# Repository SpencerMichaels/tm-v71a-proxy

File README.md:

# TM-V71A display proxy

A small board that sits in the cable between a **Kenwood TM-V71A** radio and its separated control head and changes its brightness based on an external 12V input — for instance, your vehicle's ILL+.

The TM-V71A has only a single display brightness setting, which is cumbersome to change, especially if you need to operate your radio in both day and night conditions. This board stores separate brightness settings depending on whether your vehicle's headlights are on or not, and switches the control head's brightness to the corresponding setting every time you toggle the headlights.

To use, just set your preferred brightness in your TM-V71A's settings menu once with your headlights off, then again with your headlights on.

*3D render of Rev B, seen from the connector edge. J3 (grey) is a simplified stand-in model.*

## How it works

When the head is separated from the body, the two talk over a 4-wire cable: power, ground, and one serial data line in each direction (57,600 baud). The body tells the head what to show, including the display brightness, as a short message `33 <level> 0D`.

- **Power, ground and the head's key presses** pass straight through the board in copper.
- **The body's display data** goes through an AVR128DB28 microcontroller. It forwards every byte to the head as it arrives, about one byte-time (0.17 ms) late, and rewrites brightness messages on the way.
- **The vehicle's lights input** (ILL+, through an optocoupler) tells the AVR whether it's day or night. The vehicle wiring is fully isolated from the radio.
- **Learning:** set the brightness in the radio's menu once with the lights off and once with them on. The board remembers both levels in EEPROM, and sends the right one whenever the lights change or the radio powers up.
- **Power:** the board takes about 5 mA from the radio's own 10 V head supply, so it needs no other power wiring.
- **Fail-safe:** with the AVR pulled from its socket and the JP1 shunt fitted, the board is a plain pass-through.

The message format and how the radio uses it are in [docs/protocol.md](docs/protocol.md).

## Status

| | |
|---|---|
| **Rev A** (`rev-a` branch) | Built and working in the vehicle with the full firmware. Its two data lines were swapped by mistake, so it needed a small rework; the `rev-a` branch documents it. |
| **Rev B** (this branch) | Rev A with the data lines corrected, a 4-pin data-tap header (J5) for logic analyzers, and a long-lead crystal that's easier to solder. Not yet fabricated. It passes ERC, DRC with schematic parity, and 25 design checks. The firmware is shared with Rev A. |

Tested with a TM-V71A in a 2013 Toyota Tacoma. Any vehicle with a 12 V lights-on (ILL+ or TAIL) signal should work.

## Building one

1. **Order the PCB.** Upload [`hardware/fab/kenwood_proxy_revB_oshpark_gerbers.zip`](hardware/fab/kenwood_proxy_revB_oshpark_gerbers.zip) to OSH Park or any 2-layer fab: 54 × 52 mm, about $22 for three at OSH Park. See [ordering notes](hardware/fab/ORDERING.md).
2. **Order the parts.** [`BOM_upload_digikey_mouser.csv`](hardware/fab/BOM_upload_digikey_mouser.csv) uploads straight to DigiKey or Mouser. Expect about $30. All parts are through-hole.
3. **Assemble and check** with the **[assembly guide](docs/assembly.md)**. Each step has a diagram of the board with that step's parts highlighted, and the guide has the meter and power checks to do before connecting the radio.
4. **Program it** with a 5 V SerialUPDI adapter: see [firmware/README.md](firmware/README.md).
5. **Print the case** (PETG or ASA) from [`hardware/enclosure/`](hardware/enclosure/): two parts, no supports, 4 × M3 screws.

6. **Install.** Body cable → J1, head cable → J2. J3 → the vehicle's ILL+ (live with the parking lights) and chassis ground. Then set the brightness once with the lights off and once with them on.

## Repository layout

| Path | What |
|---|---|
| [`hardware/`](hardware/) | KiCad 10 project, Gerbers, BOMs, design checks, SPICE simulation, and the generator scripts. [Design notes](hardware/README.md). |
| [`hardware/enclosure/`](hardware/enclosure/) | Case STLs and STEP, plus the FreeCAD generator script |
| [`firmware/`](firmware/) | AVR firmware (arduino-cli + DxCore), host unit tests, serial tools |
| [`docs/assembly.md`](docs/assembly.md) | Rev B assembly and checks |
| [`docs/protocol.md`](docs/protocol.md) | The head ↔ body link, as measured |
| [`docs/captures/`](docs/captures/) | Raw captures of the radio's traffic |
| [`docs/research/`](docs/research/) | Service-manual notes on the radio's interface and the Tacoma lighting circuit |

## Safety notes

- The cable's PB line carries about 10 V. A reversed or miswired 4P4C coupler can put it on a data pin of the head. The assembly guide checks every J2 pin before the head is connected.
- **Fit the JP1 shunt only with the AVR removed.**
- The board never draws power from vehicle wiring. The lights input is opto-isolated and simulated to survive reversed wiring, 24 V and a 40 V load dump.

## License

- **Hardware** (everything under `hardware/` except the Python scripts: schematic, PCB, Gerbers, BOMs, case models): [CERN-OHL-S-2.0](LICENSE-HARDWARE).
- **Firmware, scripts and tools:** [GPL-3.0](LICENSE).
- **Documentation:** follows the hardware or software it describes.

## Credits

- The brightness message format was first published by [KK4HEJ](https://kk4hej.wordpress.com/decoding-the-tm-v71a-display-protocol/).
- The 4P4C jack footprint follows Würth Elektronik's [KiCad library](https://github.com/WurthElektronik/KiCad-Library).
- Built with KiCad, Freerouting, ngspice, FreeCAD and DxCore.

Kenwood and TM-V71A are trademarks of JVCKENWOOD Corporation. This project isn't affiliated with or endorsed by Kenwood.

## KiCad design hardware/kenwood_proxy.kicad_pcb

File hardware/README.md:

# Hardware: Rev B

The KiCad 10 project for the proxy board: a 54 × 52 mm, 2-layer, all-through-hole board for hand assembly.

| File | What |
|---|---|
| `kenwood_proxy.kicad_pro` / `.kicad_sch` / `.kicad_pcb` | The KiCad project, with three schematic sheets |
| `fab/` | Gerbers (OSH Park zip), BOMs, [ordering notes](fab/ORDERING.md) |
| `enclosure/` | 3D-printable case: STL, STEP and the generator; see its [README](enclosure/README.md) |
| `checks/` | Schematic PDF, layout PDF (1:1), ERC/DRC reports, design-check results, netlist |
| `build_schematic.py`, `build_board.py`, `check_design.py` | Scripts that generate and check the design (see [Rebuilding](#rebuilding)) |
| `simulation/`, [`simulation_review.md`](simulation_review.md) | ngspice checks of the interface, ILL input and power networks |
| `footprints/`, `Kenwood_Proxy.kicad_sym` | Project footprint (4P4C jack) and symbol library |
| `3dmodels/` | Simplified Micro-Fit (J3) model and its generator, since KiCad's library has none |

**Rev B status.** Rev B is Rev A with three changes:
- the data-line fix
- the J5 tap header
- a long-lead crystal

The design has been verified on a **reworked Rev A board** in a vehicle, and the firmware is the same. Rev B itself hasn't been fabricated yet. It passes ERC, DRC with schematic parity, and the design checks.

## Circuit

| Block | What it does |
|---|---|
| **Pass-through** | J1 (BODY) and J2 (HEAD) are Würth 615004143821 4P4C jacks. PB (pin 1), GND (pin 2) and the head → body data line (pin 4) run straight through in copper. |
| **Proxy, body → head** | The body's data (J1 pin 3) goes only to the AVR, through R6 10 kΩ. The AVR re-sends every byte to the head (J2 pin 3) on USART1 TX through R2 470 Ω, rewriting brightness messages on the way. |
| **Idle and reset** | The head's input has its own 47 kΩ pull-up. While the AVR is in reset, being programmed or removed, the line idles high and the display keeps its last content. |
| **JP1 bypass** | Recovery only: **remove U1, then fit the shunt** to connect body data straight to the head. With U1 running, JP1 makes the AVR and the body fight over the line. Nothing is damaged (simulated peaks are 10 mA at the AVR pin and 5 mA at the body's driver), but the data is garbled. |
| **Power** | PB (about 10 V from the radio's regulator) → R1 150 Ω 1 W → RC filter (C6, C5) → LM2936Z-5.0 → 5 V. Draws about 5 mA. The board never takes power from vehicle wiring. R1 limits fault current, and the voltage across it ÷ 150 gives the board's current. |
| **Lights input** | J3 (Molex Micro-Fit 3.0, latching): pin 1 ILL+, pin 2 GND. R9 2.2 kΩ, R10 680 Ω shunt, D1 reverse protection, then an SFH617A-3 optocoupler. ILL_SENSE (PD1) reads low when the lights are on. The vehicle side is isolated from the radio's ground. |
| **J4: programming** | 1 GND, 2 UPDI, 3 DBG_TX (event log, through R13). |
| **J5: data taps** | 1 GND, 2 body → head (through R6), 3 head → body (through R7), 4 what the head receives (after R2). Listen only. |
| **Crystal** | Y1, 32.768 kHz, auto-tunes the AVR's internal 20 MHz oscillator, so the UART timing holds over temperature. |

**Lights input, simulated:**
- reads low (0.36 V or less) with ILL+ from 9 V upward
- reads high (5.0 V) with ILL+ at 2 V or below
- survives reversed wiring (D1), 24 V, and a 40 V load dump (R9 is rated 0.5 W)

## MCU pins (AVR128DB28, SPDIP-28)

| Pin | Port | Function |
|---|---|---|
| 23 | PA1 | USART0 RX ← body data, through R6 |
| 22 | PA0 | USART0 TX → DBG_TX on J4 pin 3 (event log, 57,600 baud) |
| 2 | PC0 | USART1 TX → R2 → head's data input |
| 3 | PC1 | head → body data, through R7 (logging only) |
| 7 | PD1 | ILL_SENSE (low = lights on) |
| 16 / 17 | PF0 / PF1 | 32.768 kHz crystal |
| 19 | UPDI | J4 pin 2 |
| 6, 14, 20 / 15, 21 | | 5 V / GND |
| others | PA2–PA7, PC2–PC3, PD2–PD7 | unused; the firmware enables pull-ups |

## Interface levels

Taken from the TM-V71A service manual; see [`docs/research/`](../docs/research/).
- **Body transmit:** a TC74HC4050 buffer through a 1 kΩ resistor.
- **Body receive:** through a 1 kΩ resistor with a 47 kΩ pull-up.
- **Head receive:** a TC4S81F gate with a 47 kΩ pull-up and a varistor.

Simulated against those values:
- the proxy's low level at the head is 0.06 V
- the low level through the JP1 bypass is 0.11 V
- JP1 fitted with U1 running gives a steady 3.5 mA of contention, which is safe

Cable corners from 100 pF to 470 pF were simulated: the default installation (a 4 m body cable, a 0.3 m head cable) plus those extremes.

## PCB layout

- **Edges:** J1, J2 and J3 sit on the top edge, with the jack faces flush. J4 is at the bottom left, J5 at the top left, and the power section runs along the bottom. There's an M3 mounting hole in each corner.
- **Routing:** Freerouting 2.1.0, plus hand-routed ILL nets.
  - Track widths: PB, PB_FILT and +5 V are 0.6 mm; signals 0.3 mm; ILL nets 0.4 mm.
  - GND pours on both layers, with stitching vias on a 3 mm grid.
- **ILL isolation:** the ILL area (top right, outlined on the silkscreen) has no pour and no other tracks. `kenwood_proxy.kicad_dru` enforces at least 2.0 mm from the ILL nets to all other copper, and the layout gives about 2.5 mm.
- **Checks:** DRC with schematic parity gives 0 violations, 0 unconnected and 0 parity errors (`checks/pcb-drc.json`). The design checks pass 25/25 (`checks/design_checks.json`).
- **3D models:**
  - The jacks use Würth's STEP model through `${WE_3DMODEL_DIR}`. Install [WurthElektronik/KiCad-Library](https://github.com/WurthElektronik/KiCad-Library) and set that path variable in KiCad to see them.
  - Y1 uses KiCad's near-identical C26-LF crystal model.
  - J3 uses `3dmodels/Molex_Micro-Fit_3.0_43045-0200_simplified.step`.
- **Jack footprint:** matches Würth's official KiCad footprint `J_Wurth_WR-MJ_615004143821` ([WurthElektronik/KiCad-Library](https://github.com/WurthElektronik/KiCad-Library)), rotated 180° and with 1.5 mm pads.

## Rebuilding

The schematic and board are generated by scripts. Edit the scripts rather than the KiCad files: **re-running a script overwrites GUI edits.**

```sh
python3 build_schematic.py                       # schematic, symbol library, design_intent.json
python3 check_design.py                          # netlist + ERC + 25 design checks -> checks/
KPY=/Applications/KiCad/KiCad.app/Contents/Frameworks/Python.framework/Versions/Current/bin/python3
$KPY build_board.py                              # placement -> checks/placement.dsn
java -jar freerouting-2.1.0.jar -de checks/placement.dsn -do checks/routing.ses -mp 40 --gui.enabled=false
$KPY build_board.py --session checks/routing.ses # import routing, pours, hand fixes
kicad-cli pcb drc --schematic-parity -o checks/pcb-drc.json kenwood_proxy.kicad_pcb
```

`build_board.py` hand-routes one PB link beside J4 that Freerouting leaves unrouted. The paths in it assume the macOS KiCad install; adjust them for other platforms.

## Possible future work

- **Follow the dash dimmer.** Wire J3 across ILL+ and ILL− instead of ILL+ and GND. The opto output then follows the dimmer's PWM, so the AVR could time the duty cycle and map it to brightness 0–8.
  - Reported automotive dimmer frequencies are 100 Hz–1 kHz, which the SFH617A and the 10 kΩ pull-up can follow, so this would be firmware-only.
  - The current firmware's 50 ms "stable" filter assumes a steady input, so it would need changing.
  - Measure the dimmer's frequency first.
- **Auto power-on** needs no hardware: the radio resumes its on/off state when DC returns, so an ACC-switched supply is enough.

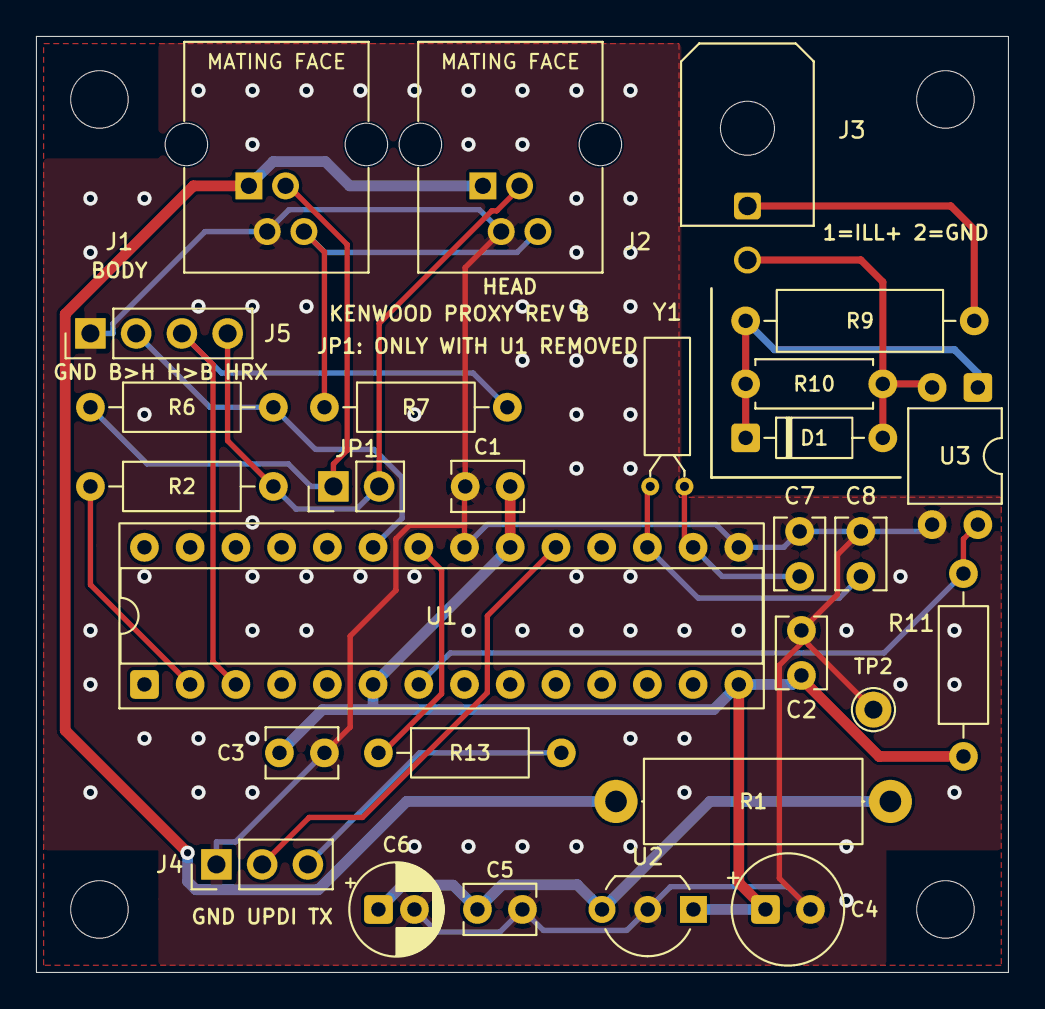
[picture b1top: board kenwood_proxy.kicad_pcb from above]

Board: 2 copper layers, 54.0 x 52.0 mm, 32 parts (0 on the bottom side), 19 nets.

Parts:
C1, C2, C3, C5: 100nF 50V X7R; C_Disc_D3.8mm_W2.6mm_P2.50mm
C4: 22uF 16V tantalum; CP_Radial_Tantal_D6.0mm_P2.50mm
C6: 10uF 25V 105C; CP_Radial_D5.0mm_P2.00mm
C7, C8: 15pF C0G; C_Disc_D3.8mm_W2.6mm_P2.50mm
D1: 1N4148; D_DO-35_SOD27_P7.62mm_Horizontal
H1, H2, H3, H4: M3; MountingHole_3.2mm_M3
J1: KENWOOD BODY; Wurth_615004143821_4P4C_TabUp
J2: KENWOOD HEAD; Wurth_615004143821_4P4C_TabUp
J3: ILL+ / GND; Molex_Micro-Fit_3.0_43045-0200_2x01_P3.00mm_Horizontal
J4: PROG/DEBUG; PinHeader_1x03_P2.54mm_Vertical
J5: DATA TAPS; PinHeader_1x04_P2.54mm_Vertical
JP1: HARD BYPASS; PinHeader_1x02_P2.54mm_Vertical
R1: 150R 1W; R_Axial_DIN0414_L11.9mm_D4.5mm_P15.24mm_Horizontal
R2, R13: 470R; R_Axial_DIN0207_L6.3mm_D2.5mm_P10.16mm_Horizontal
R6, R7, R11: 10k; R_Axial_DIN0207_L6.3mm_D2.5mm_P10.16mm_Horizontal
R9: 2.2k; R_Axial_DIN0309_L9.0mm_D3.2mm_P12.70mm_Horizontal
R10: 680R; R_Axial_DIN0207_L6.3mm_D2.5mm_P7.62mm_Horizontal
TP2: GND; TestPoint_THTPad_D2.0mm_Drill1.0mm
U1: AVR128DB28-I/SP; DIP-28_W7.62mm_Socket
U2: LM2936Z-5.0; TO-92_Inline_Wide
U3: SFH617A-3; DIP-4_W7.62mm
Y1: 32.768kHz 12.5pF; Crystal_DS26_D2.0mm_L6.0mm_Horizontal

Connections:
+5V: C1.1, C2.1, C3.1, C4.1, R11.1, U1.6 (VDDIO2), U1.14 (AVDD), U1.20 (VDD), U2.1 (VO)
BODY_TXD: J1.3 (DATA_body-to-head), JP1.1, R6.1
DBG_TX: J4.3, R13.2
DBG_TX_MCU: R13.1, U1.22 (XTALHF1/PA0)
GND: C1.2, C2.2, C3.2, C4.2, C5.2, C6.2, C7.2, C8.2, J1.2 (GND), J2.2 (GND), J4.1, J5.1, TP2.1, U1.15 (AGND), U1.21 (GND), U2.2 (GND), U3.3
HEAD_RXD: J2.3 (DATA_body-to-head), J5.4, JP1.2, R2.2
HEAD_TXD: J1.4 (DATA_head-to-body), J2.4 (DATA_head-to-body), R7.1
HEAD_TX_MCU: R2.1, U1.2 (PC0)
ILL_GND: D1.2 (A), J3.2, R10.2, U3.2
ILL_LED_A: D1.1 (K), R9.2, R10.1, U3.1
ILL_P: J3.1, R9.1
ILL_SENSE: R11.2, U1.7 (PD1), U3.4
PB: J1.1 (PB), J2.1 (PB), R1.1
PB_FILT: C5.1, C6.1, R1.2, U2.3 (VI)
TAP_BODY: J5.2, R6.2, U1.23 (XTALHF2/PA1)
TAP_HEAD: J5.3, R7.2, U1.3 (PC1)
UPDI: J4.2, U1.19 (UPDI)
XTAL32K1: C7.1, U1.16 (XTAL32K1/PF0), Y1.1
XTAL32K2: C8.1, U1.17 (XTAL32K2/PF1), Y1.2

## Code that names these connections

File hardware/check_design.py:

"""Kenwood proxy design checks. Exports the native KiCad netlist and ERC, then checks
pin-level connectivity against design_intent.json plus explicit safety requirements.
Does not simulate parts; electrical limits below are hand calculations from datasheets.
"""
from pathlib import Path
import json, subprocess, xml.etree.ElementTree as ET

HERE = Path(__file__).resolve().parent
CHK = HERE/'checks'; CHK.mkdir(exist_ok=True)
SCH = HERE/'kenwood_proxy.kicad_sch'
subprocess.run(['kicad-cli','sch','export','netlist','--format','kicadxml','-o',str(CHK/'netlist.xml'),str(SCH)],check=True,capture_output=True)
subprocess.run(['kicad-cli','sch','erc','--format','json','--severity-all','-o',str(CHK/'erc.json'),str(SCH)],check=True,capture_output=True)

intent = json.loads((HERE/'design_intent.json').read_text())
root = ET.parse(CHK/'netlist.xml').getroot()
actual = {}; nets = {}
for n in root.iter('net'):
    name = n.get('name').lstrip('/')
    for nd in n.iter('node'):
        actual[(nd.get('ref'), nd.get('pin'))] = name
        nets.setdefault(name, set()).add((nd.get('ref'), nd.get('pin')))

results = []
def check(name, ok, detail=''):
    results.append({'check': name, 'pass': bool(ok), 'detail': detail})

# 1. ERC clean
erc = json.loads((CHK/'erc.json').read_text())
viol = [v for s in erc['sheets'] for v in s['violations']]
check('ERC: zero violations', not viol, '; '.join(v['description'] for v in viol))

# 2. Every intended pin is on its intended net (unconnected pins must be absent or single-pin)
bad = []
for ref, c in intent.items():
    if ref.startswith('#'): continue
    for pin, p in c['pins'].items():
        got = actual.get((ref, pin))
        want = p['net']
        if want is None:
            if got is not None and len(nets.get(got, ())) > 1: bad.append(f'{ref}.{pin} should be NC, is on {got}')
        elif got != want: bad.append(f'{ref}.{pin} want {want} got {got}')
check('Netlist parity with design intent', not bad, '; '.join(bad))

def on(net, ref, pin): return (ref, pin) in nets.get(net, set())

# 3. Jack pin mapping (Wurth numbering, user-confirmed physical order)
for j in ('J1', 'J2'):
    check(f'{j} pin1 PB / pin2 GND / pin3 HEAD_TXD',
          actual.get((j,'1'))=='PB' and actual.get((j,'2'))=='GND' and actual.get((j,'3'))=='HEAD_TXD')
check('J1 pin4 = BODY_TXD, J2 pin4 = HEAD_RXD (no TX/RX crossover)', actual.get(('J1','4'))=='BODY_TXD' and actual.get(('J2','4'))=='HEAD_RXD')
check('HEAD_TXD direct copper J2.3 to J1.3', on('HEAD_TXD','J1','3') and on('HEAD_TXD','J2','3'))

# 4. PB never touches any MCU, opto, or signal net; PB only reaches U2 through R1
pb_nets = {'PB','PB_FILT'}
pb_refs = {r for n in pb_nets for r,_ in nets.get(n,())}
check('PB nets touch only jacks, R1, C5, C6, U2 and PWR_FLAG', pb_refs <= {'J1','J2','R1','C5','C6','U2','#FLG1'}, str(sorted(pb_refs)))
check('PB direct copper J1.1 to J2.1; board supply via R1', on('PB','J1','1') and on('PB','J2','1') and on('PB','R1','1') and on('PB_FILT','R1','2'))

# 5. Full-proxy data path: body -> MCU (tap) -> R2 -> head; JP1 is the only direct body/head bridge
hr = nets['HEAD_RXD']
check('HEAD_RXD connections limited to J2, JP1, R2', {r for r,_ in hr} <= {'J2','JP1','R2'}, str(sorted(hr)))
check('BODY_TXD connections limited to J1, JP1, R6 (tap)', {r for r,_ in nets['BODY_TXD']} <= {'J1','JP1','R6'}, str(sorted(nets['BODY_TXD'])))
check('Proxy output: U1 pin 2 (PC0, USART1 TX) -> R2 -> HEAD_RXD', on('HEAD_TX_MCU','U1','2') and on('HEAD_TX_MCU','R2','1') and on('HEAD_RXD','R2','2') and {r for r,_ in nets['HEAD_TX_MCU']} <= {'U1','R2'})
check('JP1 hard bypass is the only part bridging BODY_TXD and HEAD_RXD', ({r for r,_ in nets['BODY_TXD']} & {r for r,_ in nets['HEAD_RXD']}) == {'JP1'} and on('BODY_TXD','JP1','1') and on('HEAD_RXD','JP1','2'))
check('No U1 pin directly on any radio-line net', not any(r=='U1' for n in ('BODY_TXD','HEAD_RXD','HEAD_TXD') for r,_ in nets.get(n,())))

# 6. ILL isolation: ILL_P/ILL_GND/ILL_LED_A never touch board nets
ill = {'ILL_P','ILL_GND','ILL_LED_A'}
ill_refs = {(r,p) for n in ill for r,p in nets.get(n,())}
check('ILL side isolated (only J3, R9, R10, D1, U3 LED pins)', {r for r,_ in ill_refs} <= {'J3','R9','R10','D1','U3'} and not ({('U3','3'),('U3','4')} & ill_refs))

# 7. UART pin plan matches AVR DB SPDIP-28 multiplexing (DS40002247B table 3-1)
plan = {'23':'TAP_BODY','22':'DBG_TX_MCU','3':'TAP_HEAD','2':'HEAD_TX_MCU','16':'XTAL32K1','17':'XTAL32K2','19':'UPDI'}
check('U1 USART0 PA1/PA0, USART1 PC1/PC0, XOSC32K PF0/PF1, UPDI', all(actual.get(('U1',k))==v for k,v in plan.items()))
check('U1 VDD/AVDD/VDDIO2 on +5V, GND/AGND on GND', all(actual.get(('U1',k))=='+5V' for k in ('6','14','20')) and all(actual.get(('U1',k))=='GND' for k in ('15','21')))

# 8. Hand calculations (datasheet values)
calc = {}
Vb = 5.0
R956 = 1000   # body TXD series resistor inside the radio (service manual p.84, IC951 3Y -> R956 1k -> J952-4)
R2 = 470; RPU_HEAD = 47000; ROUT_MCU_MAX = 117   # head CP913 pull-up (p.74); AVR output resistance worst case (VDD-0.7 V at 6 mA)
calc['proxy_low_at_head_V'] = 5.25*(R2+ROUT_MCU_MAX)/(R2+ROUT_MCU_MAX+RPU_HEAD)       # MCU low against head pull-up
calc['proxy_head_rc_us'] = (R2+ROUT_MCU_MAX)*570e-12*1e6                                # worst head-side C: 470 pF cable + 100 pF varistor
calc['jp1_with_u1_contention_mA'] = 5.25/(R956+25+R2+25)*1000                           # JP1 fitted while U1 still drives (misuse)
calc['jp1_bypass_low_at_head_V'] = 5.25*(R956+25)/(R956+25+RPU_HEAD)                    # U1 removed, JP1 fitted
def rv(ref):
    x = intent[ref]['value'].split()[0].lower()
    return float(x[:-1])*1e3 if x.endswith('k') else float(x.rstrip('r'))
R9, R10 = rv('R9'), rv('R10')
calc['ill_led_mA_at_13V'] = (13-1.15)/R9*1000 - 1.15/R10*1000
calc['ill_led_mA_at_9V'] = (9-1.15)/R9*1000 - 1.15/R10*1000
calc['ill_R9_W_at_14V'] = ((14-1.15)/R9)**2*R9
calc['ill_led_mA_at_2V'] = max(0.0, (2.0-1.15)/R9*1000 - 1.15/R10*1000)   # ILL+ residual/floating 2 V with lights off: R10 shunts all of it
calc['pb_fault_current_mA_R1_short'] = 10/150*1000
calc['R1_fault_W'] = 10**2/150
calc['est_board_current_mA'] = {'mcu_20MHz_active_typ':4.4,'ldo_iq':0.2,'opto_pullup_max':0.5,'taps':0.0}
calc['est_board_total_mA'] = round(sum(calc['est_board_current_mA'].values()),2)
check('Proxy low level at head < 1.5 V (TC4S81F VIL max)', calc['proxy_low_at_head_V'] < 1.5, f"{calc['proxy_low_at_head_V']:.2f} V")
check('Proxy edge RC at head < 1 us (bit = 17.4 us)', calc['proxy_head_rc_us'] < 1.0, f"{calc['proxy_head_rc_us']:.2f} us")
check('JP1 fitted with U1 present: contention <= 4 mA (HC4050 recommended)', calc['jp1_with_u1_contention_mA'] <= 4.0, f"{calc['jp1_with_u1_contention_mA']:.2f} mA")
check('JP1 bypass (U1 removed) low level at head < 1.5 V', calc['jp1_bypass_low_at_head_V'] < 1.5, f"{calc['jp1_bypass_low_at_head_V']:.2f} V")
check('ILL LED off with ILL+ at 2 V (lights off)', calc['ill_led_mA_at_2V'] == 0.0, f"{calc['ill_led_mA_at_2V']:.2f} mA")
check('ILL LED current >= 1.0 mA at 9 V input', calc['ill_led_mA_at_9V'] >= 1.0, f"{calc['ill_led_mA_at_9V']:.2f} mA")
check('Estimated board draw <= 10 mA PB target', calc['est_board_total_mA'] <= 10, f"{calc['est_board_total_mA']} mA (typical, not measured)")

out = {'results': results, 'calculations': calc, 'net_count': len(nets)}
(CHK/'design_checks.json').write_text(json.dumps(out, indent=2)+'\n')
for r in results: print(('PASS ' if r['pass'] else 'FAIL ')+r['check']+(' -- '+r['detail'] if r['detail'] and not r['pass'] else (' ('+r['detail']+')' if r['detail'] else '')))
print(f"{sum(r['pass'] for r in results)}/{len(results)} checks passed")
raise SystemExit(0 if all(r['pass'] for r in results) else 1)

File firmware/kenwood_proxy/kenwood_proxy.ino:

/* Kenwood TM-V71A proxy firmware, AVR128DB28 (DxCore).
 *
 * Pins (see hardware/README.md):
 *   Rev B (KP_BODY_ON_USART1 = 0, default):
 *     PA1 USART0 RX  <- R6 <- J1 pin 3 (body -> head stream)
 *     PC0 USART1 TX  -> R2 470 ohm -> J2 pin 3 (head RX, proxy output)
 *     PC1            <- R7 <- cable pin 4 (head -> body, passes straight through; unused)
 *   Reworked Rev A (KP_BODY_ON_USART1 = 1, rev-a branch):
 *     PC1 USART1 RX  <- R7 <- J1 pin 3 (body -> head stream)
 *     PC0 USART1 TX  -> 470 ohm -> J2 pin 3
 *   PA0 USART0 TX  -> DBG_TX on J4 pin 3 (event log, radio baud)
 *   PD1            <- ILL_SENSE (low = lights on)
 *   PF0/PF1        32.768 kHz crystal: auto-tunes the internal oscillator
 *
 * All packet decisions live in proxy_core.c (host-tested). This file only moves
 * bytes, samples the lights input, stores EEPROM and kicks the watchdog. Arduino's
 * Serial is not used, so the USART interrupts below are the only ones.
 */
#include <avr/io.h>
#include <avr/interrupt.h>
#include <avr/eeprom.h>
extern "C" {
#include "proxy_core.h"
}

static kp_proxy_t P;

/* ---------------------------------------------------------------- EEPROM */
/* Layout: magic, version, slot day, slot night, last body level, checksum. */
#define EE_MAGIC 0x4B   /* 'K' */
#define EE_VER   1
static uint8_t ee_sum(const kp_persist_t *s) { return (uint8_t)(EE_MAGIC ^ s->slot[0] ^ (s->slot[1] << 1) ^ (s->last_body << 2) ^ 0x5A); }

static void ee_load(kp_persist_t *s)
{
    s->slot[0] = eeprom_read_byte((uint8_t *)2);
    s->slot[1] = eeprom_read_byte((uint8_t *)3);
    s->last_body = eeprom_read_byte((uint8_t *)4);
    if (eeprom_read_byte((uint8_t *)0) != EE_MAGIC || eeprom_read_byte((uint8_t *)1) != EE_VER ||
        eeprom_read_byte((uint8_t *)5) != ee_sum(s))
        s->slot[0] = s->slot[1] = s->last_body = KP_UNSET;   /* blank or corrupt: start fresh */
}

static void ee_store(const kp_persist_t *s)
{
    /* update_byte skips unchanged cells. Interrupts stay on, so forwarding continues. */
    eeprom_update_byte((uint8_t *)0, EE_MAGIC);
    eeprom_update_byte((uint8_t *)1, EE_VER);
    eeprom_update_byte((uint8_t *)2, s->slot[0]);
    eeprom_update_byte((uint8_t *)3, s->slot[1]);
    eeprom_update_byte((uint8_t *)4, s->last_body);
    eeprom_update_byte((uint8_t *)5, ee_sum(s));
}

/* ---------------------------------------------------------------- debug log */
static uint8_t dbg[64];
static volatile uint8_t dbg_head, dbg_tail;

static void dbg_putc(uint8_t c)
{
    uint8_t next = (dbg_head + 1) & 63;
    if (next == dbg_tail) return;              /* log is best effort */
    dbg[dbg_head] = c;
    dbg_head = next;
    USART0.CTRLA |= USART_DREIE_bm;
}

static void on_event(uint8_t ev, uint8_t a, uint8_t b)
{
    /* Called from the RX interrupt or with interrupts off: keep it short. */
    if (KP_SNIFF) return;                      /* sniff build: DBG_TX carries raw body bytes only */
    dbg_putc(ev);
    if (a) { dbg_putc(' '); dbg_putc(a); }
    if (b) { dbg_putc(' '); dbg_putc(b); }
    dbg_putc('\r');
    dbg_putc('\n');
}

static void dbg_str(const char *s)
{
    if (KP_SNIFF) return;
    uint8_t sreg = SREG;
    cli();
    while (*s) dbg_putc((uint8_t)*s++);
    SREG = sreg;
}

static char lvl_char(uint8_t v) { return v == KP_UNSET ? '-' : (char)v; }

/* ---------------------------------------------------------------- interrupts */
#if KP_BODY_ON_USART1
#define BODY_USART USART1
ISR(USART1_RXC_vect)
#else
#define BODY_USART USART0
ISR(USART0_RXC_vect)
#endif
{
    BODY_USART.RXDATAH;                        /* status first; a framing error is forwarded as received */
    uint8_t b = BODY_USART.RXDATAL;
    if (KP_SNIFF) dbg_putc(b);                 /* same baud in and out, so the copy keeps up */
    kp_body_byte(&P, b, millis());
    USART1.CTRLA |= USART_DREIE_bm;
}

ISR(USART1_DRE_vect)
{
    int c = kp_next_head_byte(&P);
    if (c < 0) USART1.CTRLA &= ~USART_DREIE_bm;
    else USART1.TXDATAL = (uint8_t)c;
}

ISR(USART0_DRE_vect)
{
    if (dbg_tail == dbg_head) { USART0.CTRLA &= ~USART_DREIE_bm; return; }
    USART0.TXDATAL = dbg[dbg_tail];
    dbg_tail = (dbg_tail + 1) & 63;
}

/* ---------------------------------------------------------------- setup */
static uint8_t lights_on(void) { return !(VPORTD.IN & PIN1_bm); }

static void clocks(void)
{
    /* 20 MHz internal (FQBN clock=20internal), auto-tuned against the 32.768 kHz crystal.
     * 20 MHz keeps clock harmonics off 144-148 MHz. */
    _PROTECTED_WRITE(CLKCTRL.XOSC32KCTRLA, CLKCTRL_ENABLE_bm | CLKCTRL_CSUT_1K_gc);
    _PROTECTED_WRITE(CLKCTRL.OSCHFCTRLA, CLKCTRL.OSCHFCTRLA | CLKCTRL_AUTOTUNE_bm);
}

static void pins(void)
{
    /* Unused I/O: pull-ups on so nothing floats. */
    for (uint8_t i = 2; i < 8; i++) (&PORTA.PIN0CTRL)[i] = PORT_PULLUPEN_bm;   /* PA2-PA7 */
    PORTC.PIN2CTRL = PORT_PULLUPEN_bm;
    PORTC.PIN3CTRL = PORT_PULLUPEN_bm;
    for (uint8_t i = 2; i < 8; i++) (&PORTD.PIN0CTRL)[i] = PORT_PULLUPEN_bm;   /* PD2-PD7 */
    /* PD1 ILL_SENSE has R11; PC1 TAP_HEAD is driven through R7. Plain inputs. */
    PORTA.OUTSET = PIN0_bm;  PORTA.DIRSET = PIN0_bm;    /* DBG_TX idles high */
    PORTC.OUTSET = PIN0_bm;  PORTC.DIRSET = PIN0_bm;    /* head RX idles high: no glitch at start */
}

static void uarts(void)
{
    const uint16_t baud = (uint16_t)((4UL * F_CPU + KP_BAUD / 2) / KP_BAUD);   /* 64*F/(16*baud) */
    USART0.BAUD = baud;
    USART0.CTRLC = USART_CMODE_ASYNCHRONOUS_gc | USART_PMODE_DISABLED_gc | USART_SBMODE_1BIT_gc | USART_CHSIZE_8BIT_gc;
    USART1.BAUD = baud;
    USART1.CTRLC = USART_CMODE_ASYNCHRONOUS_gc | USART_PMODE_DISABLED_gc | USART_SBMODE_1BIT_gc | USART_CHSIZE_8BIT_gc;
#if KP_BODY_ON_USART1
    USART0.CTRLB = USART_TXEN_bm;                  /* debug log only */
    USART1.CTRLB = USART_RXEN_bm | USART_TXEN_bm;  /* body in on PC1, head out on PC0 */
    USART1.CTRLA = USART_RXCIE_bm;
#else
    USART0.CTRLB = USART_RXEN_bm | USART_TXEN_bm;
    USART0.CTRLA = USART_RXCIE_bm;
    USART1.CTRLB = USART_TXEN_bm;
#endif
}

void setup()
{
    pins();
    clocks();
    kp_persist_t s;
    ee_load(&s);
    uint32_t now = millis();
    kp_init(&P, &s, lights_on(), now, on_event);
    uarts();
    _PROTECTED_WRITE(WDT.CTRLA, WDT_PERIOD_256CLK_gc);   /* ~0.26 s */

    char banner[] = "KP v1 rw=? d=? n=? b=? x\r\n";
    banner[9] = KP_ENABLE_REWRITE ? '1' : '0';
    banner[13] = lvl_char(P.pers.slot[KP_DAY]);
    banner[17] = lvl_char(P.pers.slot[KP_NIGHT]);
    banner[21] = lvl_char(P.pers.last_body);
    banner[23] = P.mode == KP_NIGHT ? 'n' : 'd';
    dbg_str(banner);
}

/* ---------------------------------------------------------------- loop */
void loop()
{
    static uint32_t last;
    static uint8_t xosc_reported;
    uint32_t now = millis();
    if (now != last) {                         /* 1 ms housekeeping */
        last = now;
        /* Crystal check, once: a 32 kHz crystal can take ~1 s to start, so look at 2 s.
         * "X 1" = running and stable; "X 0" = not running (internal clock runs untuned). */
        if (!xosc_reported && now >= 2000) {
            xosc_reported = 1;
            dbg_str((CLKCTRL.MCLKSTATUS & CLKCTRL_XOSC32KS_bm) ? "X 1\r\n" : "X 0\r\n");
        }
        uint8_t night = lights_on();
        cli();
        kp_ill_sample(&P, night, now);
        kp_tick(&P, now);
        if (kp_out_pending(&P)) USART1.CTRLA |= USART_DREIE_bm;
        uint8_t save = kp_save_due(&P, now);
        kp_persist_t s = P.pers;
        if (save) kp_saved(&P);
        sei();
        if (save) {
            ee_store(&s);
            dbg_str("W\r\n");
        }
    }
    __builtin_avr_wdr();
}

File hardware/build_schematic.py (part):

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res(s,'R1',63.5,50.8,'150R 1W','PB','PB_FILT',mpn='FMP100JR-52-150R',fp=FP['R1W'],note='5%, 1 W flameproof. Limits PB fault current (~67 mA into a short), RC-isolates MCU noise from PB, and doubles as board-current sense (V/150)')
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cap(s,'C5',127.0,63.5,'100nF 50V X7R','PB_FILT',mpn='C320C104K5R5TA',mfg='KEMET')
s.comp('U2',LDO,165.1,50.8,{'1':'+5V','2':'GND','3':'PB_FILT'},'LM2936Z-5.0',FP['TO92'],'LM2936Z-5.0/NOPB','Texas Instruments','TO-92 1=OUT 2=GND 3=IN. 40 V operating, 15 uA Iq. COUT >= 10 uF with 0.3-8 ohm ESR. Drop-in alt (same pinout): Diodes AP7381-50V-A',fields=[(165.1,40.64),(165.1,43.18)])
s.comp('C4',CP,203.2,63.5,{'1':'+5V','2':'GND'},'22uF 16V tantalum',FP['CTANT'],'T350F226K016AT','KEMET','Dipped tantalum, 6.0 mm dia, 2.54 mm pitch; ESR within LM2936 0.3-8 ohm stability window (also fine for alt U2 AP7381-50V-A)')
tp(s,'TP2',254.0,88.9,'GND')
flag(s,1,127.0,88.9,'PB_FILT'); flag(s,2,279.4,88.9,'GND')
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       'Micro-Fit 3.0 2-circuit dual-row right-angle header, latching. Mates with 2-circuit receptacle 43025-0200 (pre-crimped 22 AWG leads are fine). Pin1 ILL+ (TAIL, R1-10), pin2 chassis GND (e.g. stereo harness ground). Optocoupler keeps truck wiring isolated from radio GND')
res(s,'R9',101.6,58.42,'2.2k','ILL_P','ILL_LED_A',mpn='MFR50SFTE52-2K2',fp=FP['R05W'],note='0.5 W metal film. ~5.4 mA at 13 V; 0.23 W at 24 V continuous; 40 V load-dump pulse 0.26 J/400 ms')
res(s,'R10',152.4,76.2,'680R','ILL_LED_A','ILL_GND',fp=FP['R762'],note='LED shunt: LED needs >~1.7 mA total input current, so leakage cannot half-turn-on the opto. Simulated')
s.comp('D1',DIODE,177.8,76.2,{'1':'ILL_LED_A','2':'ILL_GND'},'1N4148',FP['DO35'],'1N4148','onsemi','Antiparallel LED reverse protection (K=pin1 on ILL_LED_A)')
s.comp('U3',OPTO,228.6,63.5,{'1':'ILL_LED_A','2':'ILL_GND','3':'GND','4':'ILL_SENSE'},'SFH617A-3',FP['DIP4'],'SFH617A-3','Vishay',
       'CTR 100-200% @10 mA, >=34% @1 mA. Isolation: ILL side never touches board GND',fields=[(228.6,50.8),(228.6,53.34)])
res(s,'R11',279.4,50.8,'10k','+5V','ILL_SENSE',note='Opto pull-up; ILL_SENSE LOW while ILL+ is on (lights on)')
s.text(25.4,101.6,'Wire J3 to ILL+ (TAIL: 11-14 V with parking/head lights on, <1 V off) and a chassis ground.\nILL_SENSE: LOW = lights on (night brightness), HIGH = lights off (day brightness).\nKeep >= 2 mm clearance between ILL nets and all board nets.')
s.comp('J4',CON3,50.8,152.4,{'1':'GND','2':'UPDI','3':'DBG_TX'},'PROG/DEBUG',FP['H3'],'TSW-103-07-G-S','Samtec',
       '0.1 in header for bench programming/logging before the board goes behind the dash. UPDI Friend (or other 5 V SerialUPDI adapter): GND + UPDI. Logging: separate 5 V USB-serial RX on DBG_TX. Never connect adapter power')
res(s,'R13',127.0,154.94,'470R','DBG_TX_MCU','DBG_TX',note='Protects PA0 if a jumper or adapter TX lands on the DBG_TX pin')
s.text(25.4,203.2,'J4: 1 GND, 2 UPDI, 3 DBG_TX (MCU -> logging adapter RX). Board stays powered from the radio (PB) while programming.')
for i,(x,y) in enumerate([(254.0,152.4),(266.7,152.4),(279.4,152.4),(292.1,152.4)],1):
    s.comp('H'+str(i),HOLE,x,y,{},'M3',FP['HOLE'],assembly='PCB_FEATURE')
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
